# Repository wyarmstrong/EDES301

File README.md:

# EDES301
Repository for EDES301 course work

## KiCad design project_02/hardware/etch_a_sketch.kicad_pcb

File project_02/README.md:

# Etch-a-Sketch PCB — EDES301 Project 2

A custom PCB for a digital Etch-a-Sketch built on the PocketBeagle. Two potentiometers control the X and Y axes on a 1.8" SPI display. Three LEDs show the current drawing color, and two buttons let you reset the canvas or cycle through colors. A USB-C port is included for expansion.

## Components
- PocketBeagle (main processor)
- HS24S010B 1.8" SPI TFT display
- 2x RK09K1110A0J potentiometers
- 3x LEDs (red, green, blue)
- 2x tactile switches
- USB-C connector
- Supporting resistors (1k, 10k, 5.1k)

## Board
- 5" x 4" 2-layer PCB
- Display and controls on front, PocketBeagle header on back

## Folder Structure
```
project_02/
  hardware/      KiCad project files
  MFG/           Gerber files
  docs/          Screenshots and mechanical drawing
  README.md
  BOM.csv
```

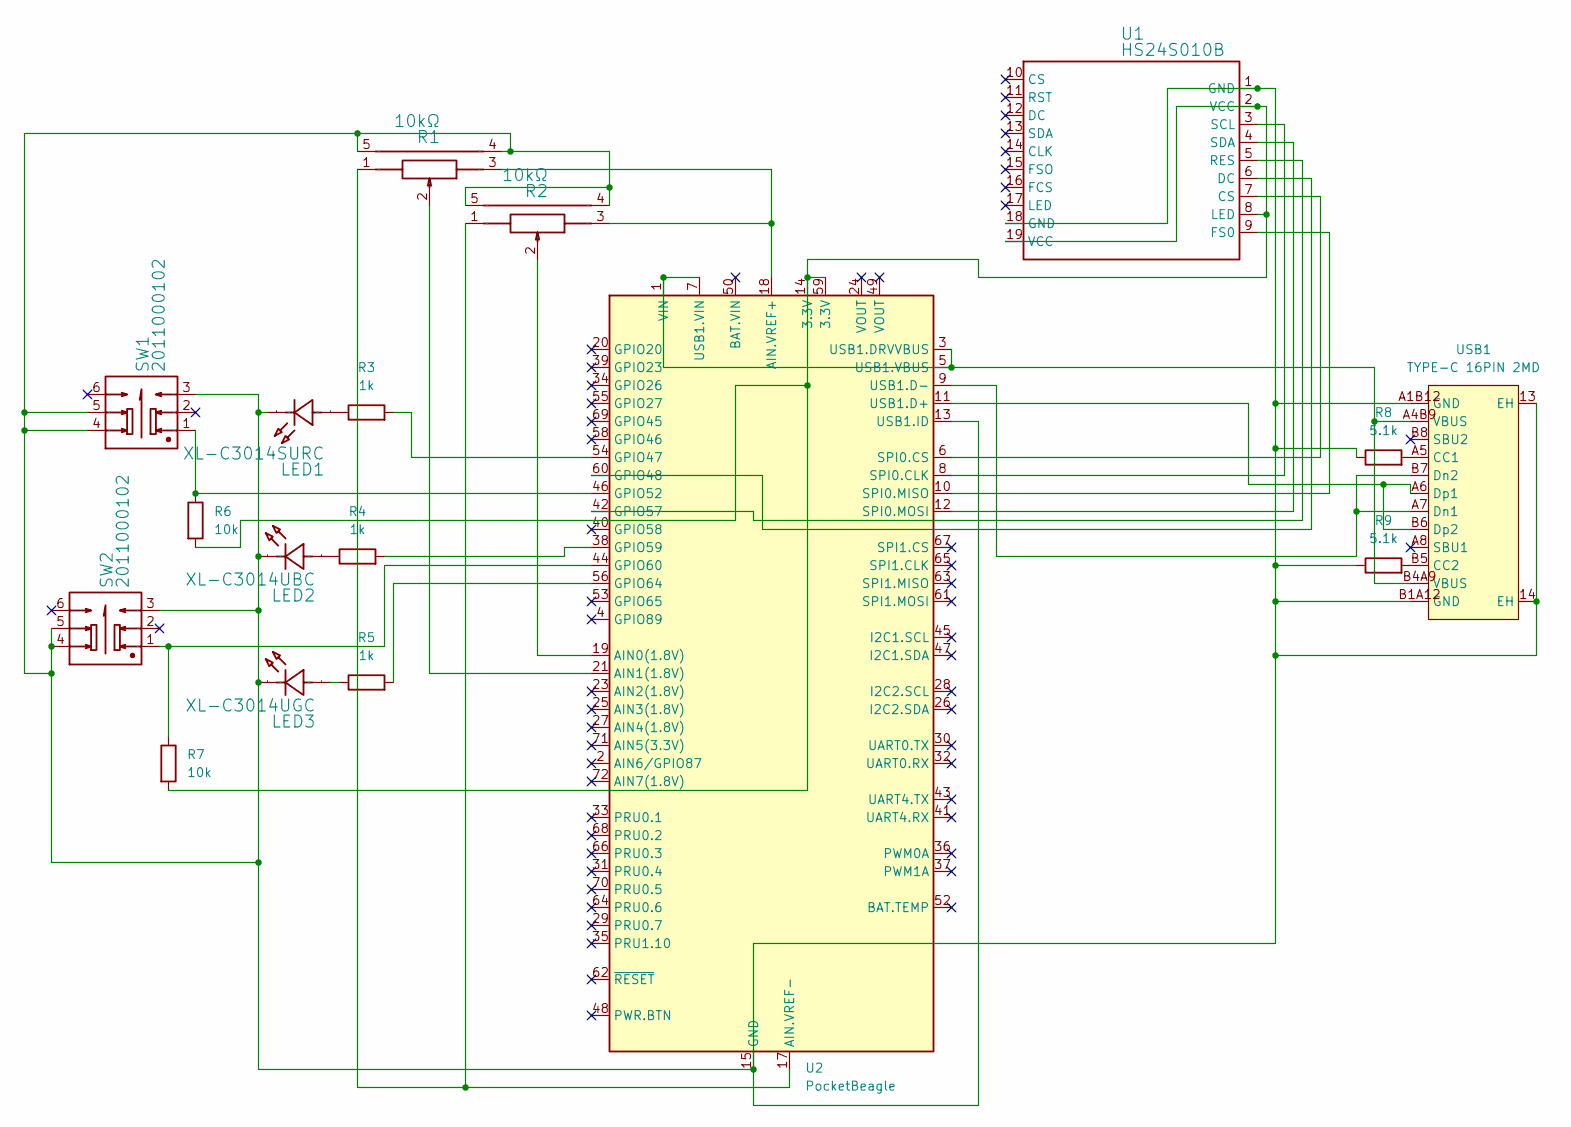
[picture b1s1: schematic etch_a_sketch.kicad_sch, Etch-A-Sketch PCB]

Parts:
LED1: XL-C3014SURC; LED-SMD_XL-C3014SURC-1; Manufacturer Part XL-C3014SURC
LED2: XL-C3014UBC; LED-SMD_L3.0-W1.3-FD-SIDE_BLUE; Manufacturer Part XL-C3014UBC
LED3: XL-C3014UGC; LED-SMD_L3.0-W1.3-RD-SIDE_GREEN; Manufacturer Part XL-C3014UGC
R1, R2: 10kΩ; RES-TH_RK09K1110A0J; Manufacturer Part RK09K1110A0J
R3, R4, R5: 1k; R_0603_1608Metric
R6, R7: 10k; R_0603_1608Metric
R8, R9: 5.1k; R_0603_1608Metric
SW1, SW2: 2011000102; SW-TH_6P-L5.8-W5.8-P2.00-LS4.5-TL; Manufacturer Part 2011000102
U1: HS24S010B; LCD-TH_L72.3-W43.0_HS24S010B; Manufacturer Part HS24S010B
U2: PocketBeagle; BeagleBoard_PocketBeagle
USB1: TYPE-C 16PIN 2MD; USB-C-SMD_TYPE-C-16PIN-2MD-073; MPN TYPE-C 16PIN 2MD(073); LCSC Part C2765186

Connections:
unnamed: LED1.2 (A), R3.1
unnamed 1: LED1.1 (K), LED2.2 (K), LED3.1 (K), R1.4 (EH), R1.5 (EH), R2.4 (EH), R2.5 (EH), R8.1, R9.1, SW1.3, SW1.4, SW1.5, SW2.3, SW2.4, SW2.5, U1.1 (GND), U1.18 (GND), U2.13 (USB1.ID), U2.15 (GND), U2.16 (GND), U2.22 (GND), U2.51 (GND), U2.57 (GND), USB1.13 (EH), USB1.14 (EH), USB1.A1B12 (GND), USB1.B1A12 (GND); also elsewhere on the board
unnamed: LED2.1 (A), R4.1
unnamed: LED3.2 (A), R5.1
unnamed: R6.2, R7.2, U1.2 (VCC), U1.8 (LED), U1.19 (VCC), U2.14 (3.3V), U2.59 (3.3V)
unnamed: U1.9 (FS0), U2.10 (SPI0.MISO)
unnamed: U1.5 (RES), U2.42 (GPIO57)
unnamed: U1.3 (SCL), U2.8 (SPI0.CLK)
unnamed: R2.2, U2.19 (AIN0(1.8V))
unnamed: R1.2, U2.21 (AIN1(1.8V))
unnamed: R1.3, R2.3, U2.18 (AIN.VREF+)
unnamed: R1.1, R2.1, U2.17 (AIN.VREF-)
unnamed: R3.2, U2.54 (GPIO47)
unnamed: U1.6 (DC), U2.60 (GPIO48)
unnamed: R6.1, SW1.1, U2.46 (GPIO52)
unnamed: R4.2, U2.38 (GPIO59)
unnamed: R7.1, SW2.1, U2.44 (GPIO60)
unnamed: R5.2, U2.56 (GPIO64)
unnamed: U1.7 (CS), U2.6 (SPI0.CS)
unnamed: U1.4 (SDA), U2.12 (SPI0.MOSI)
unnamed 20: U2.11 (USB1.D+), USB1.A6 (Dp1), USB1.B6 (Dp2); also elsewhere on the board
unnamed 21: U2.9 (USB1.D-), USB1.A7 (Dn1), USB1.B7 (Dn2); also elsewhere on the board
unnamed 22: U2.1 (VIN), U2.3 (USB1.DRVVBUS), U2.5 (USB1.VBUS), U2.7 (USB1.VIN), USB1.A4B9 (VBUS), USB1.B4A9 (VBUS); also elsewhere on the board
unnamed 23: R8.2, USB1.A5 (CC1); also elsewhere on the board
unnamed 24: R9.2, USB1.B5 (CC2); also elsewhere on the board

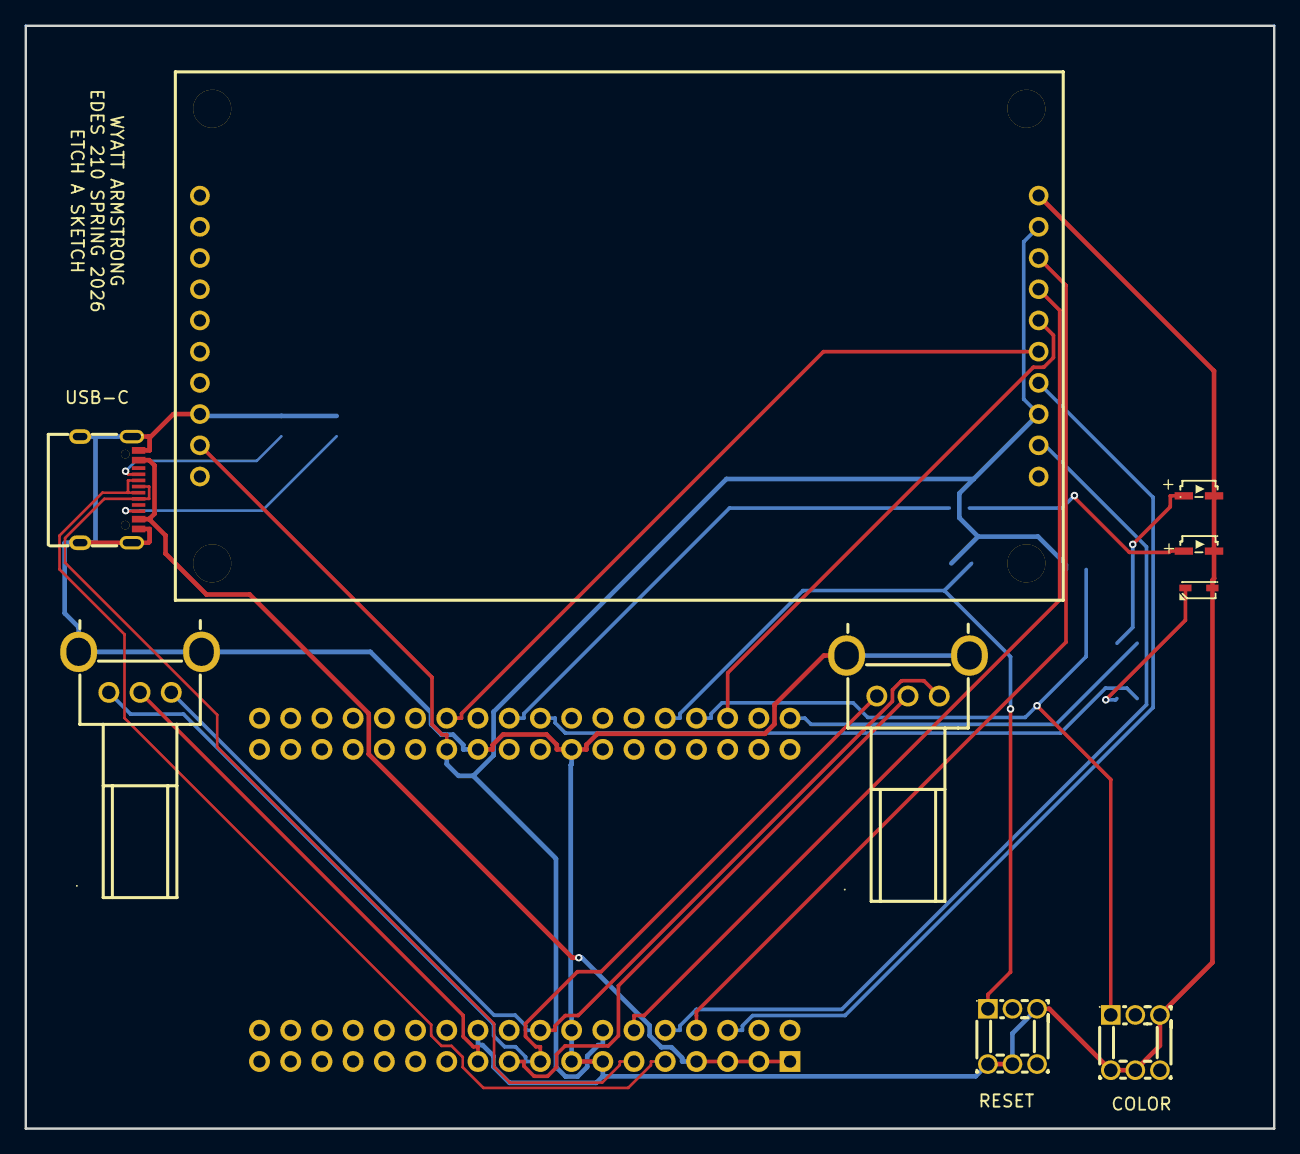
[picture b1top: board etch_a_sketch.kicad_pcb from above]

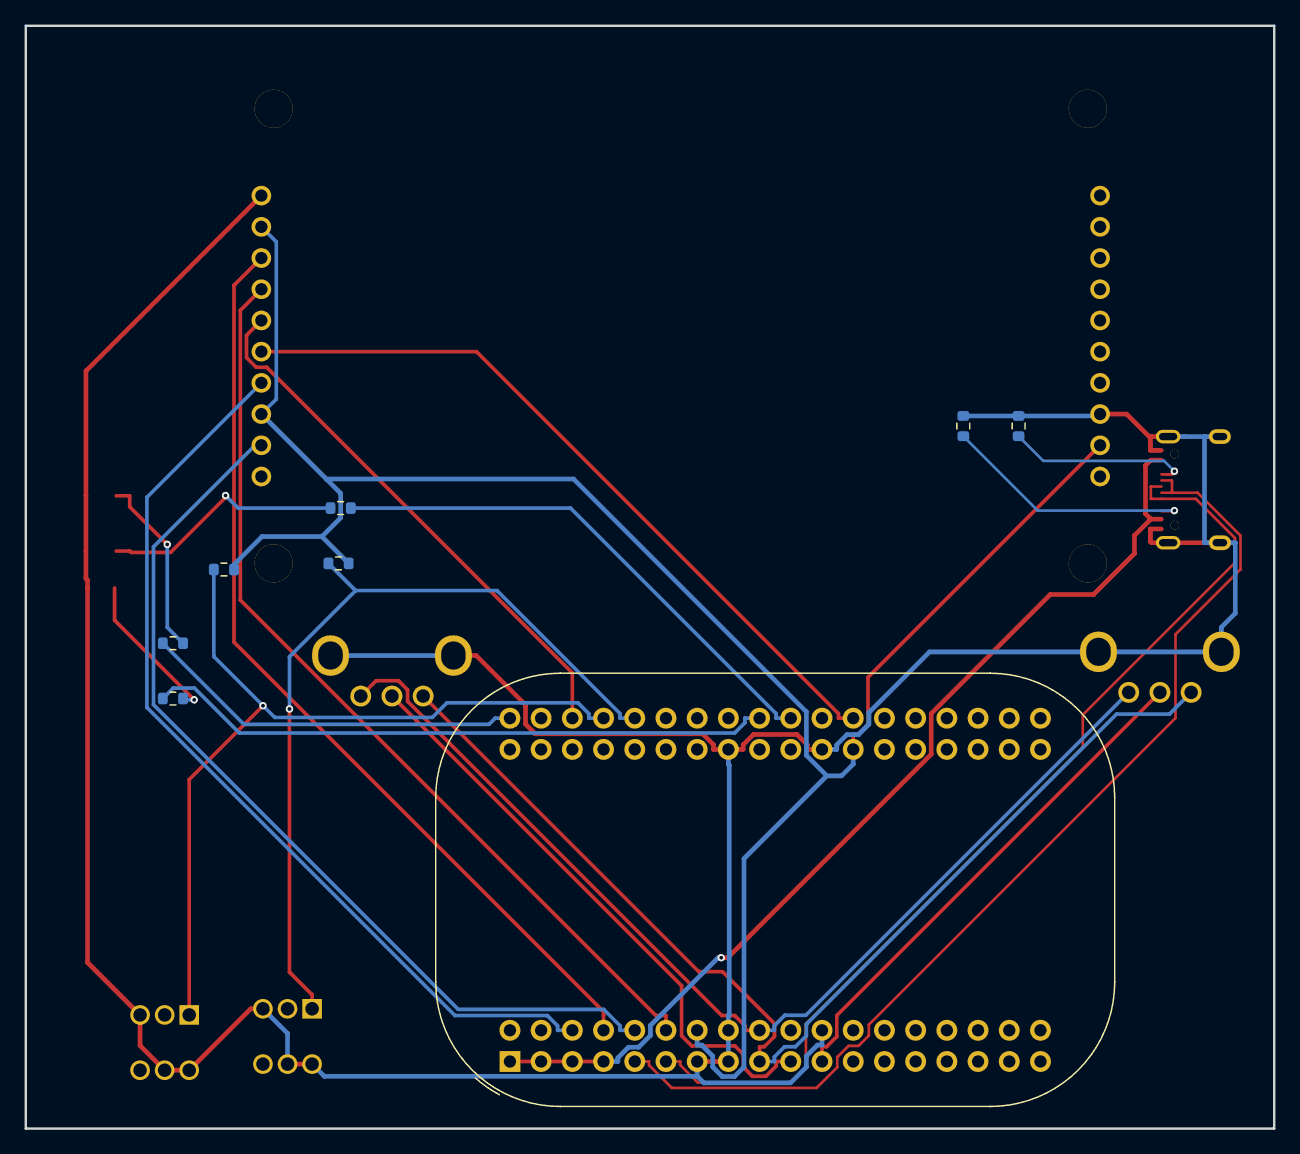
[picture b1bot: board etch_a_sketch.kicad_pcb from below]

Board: 2 copper layers, 101.6 x 89.8 mm, 17 parts (8 on the bottom side), 25 nets.

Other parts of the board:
USB-C: TYPE-C 16PIN 2MD; USB-C-SMD_TYPE-C-16PIN-2MD-073

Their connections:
unnamed 1: USB-C.13 (EH), USB-C.14 (EH), USB-C.A1B12 (GND), USB-C.B1A12 (GND); also elsewhere on the board
unnamed 20: USB-C.A6 (Dp1), USB-C.B6 (Dp2); also elsewhere on the board
unnamed 21: USB-C.A7 (Dn1), USB-C.B7 (Dn2); also elsewhere on the board
unnamed 22: USB-C.A4B9 (VBUS), USB-C.B4A9 (VBUS); also elsewhere on the board
unnamed 23: USB-C.A5 (CC1); also elsewhere on the board
unnamed 24: USB-C.B5 (CC2); also elsewhere on the board

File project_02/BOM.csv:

Designator,Manufacturer,MPN,Quantity,Description
U2,BeagleBoard,PocketBeagle,1,Single-board computer ARM Cortex-A8 1GHz 512MB RAM
U1,HS (Hansheng),HS24S010B,1,1.8 inch SPI TFT LCD Display
USB1,SHOU HAN,TYPE-C 16PIN 2MD,1,USB-C 16-pin connector
R1,ALPSALPINE,RK09K1110A0J,1,10k Ohm Potentiometer X-axis
R2,ALPSALPINE,RK09K1110A0J,1,10k Ohm Potentiometer Y-axis
LED1,XINGLIGHT,XL-C3014SURC,1,Red LED SMD 3014
LED2,XINGLIGHT,XL-C3014UBC,1,Blue LED SMD 3014
LED3,XINGLIGHT,XL-C3014UGC,1,Green LED SMD 3014
SW1,SAMZO,2011000102,1,Tactile switch 6-pin Reset
SW2,SAMZO,2011000102,1,Tactile switch 6-pin Color Change
R3,Generic,RC0603FR-071KL,1,1k Ohm 0603 Resistor LED1 current limit
R4,Generic,RC0603FR-071KL,1,1k Ohm 0603 Resistor LED2 current limit
R5,Generic,RC0603FR-071KL,1,1k Ohm 0603 Resistor LED3 current limit
R6,Generic,RC0603FR-0710KL,1,10k Ohm 0603 Resistor SW1 pull-up
R7,Generic,RC0603FR-0710KL,1,10k Ohm 0603 Resistor SW2 pull-up
R8,Generic,RC0603FR-075K1L,1,5.1k Ohm 0603 Resistor USB-C CC1 pull-down
R9,Generic,RC0603FR-075K1L,1,5.1k Ohm 0603 Resistor USB-C CC2 pull-down

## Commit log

2026-02-02 Updating README.md
2026-05-05 assignment 4
2026-05-05 proj 2
2026-05-05 files
